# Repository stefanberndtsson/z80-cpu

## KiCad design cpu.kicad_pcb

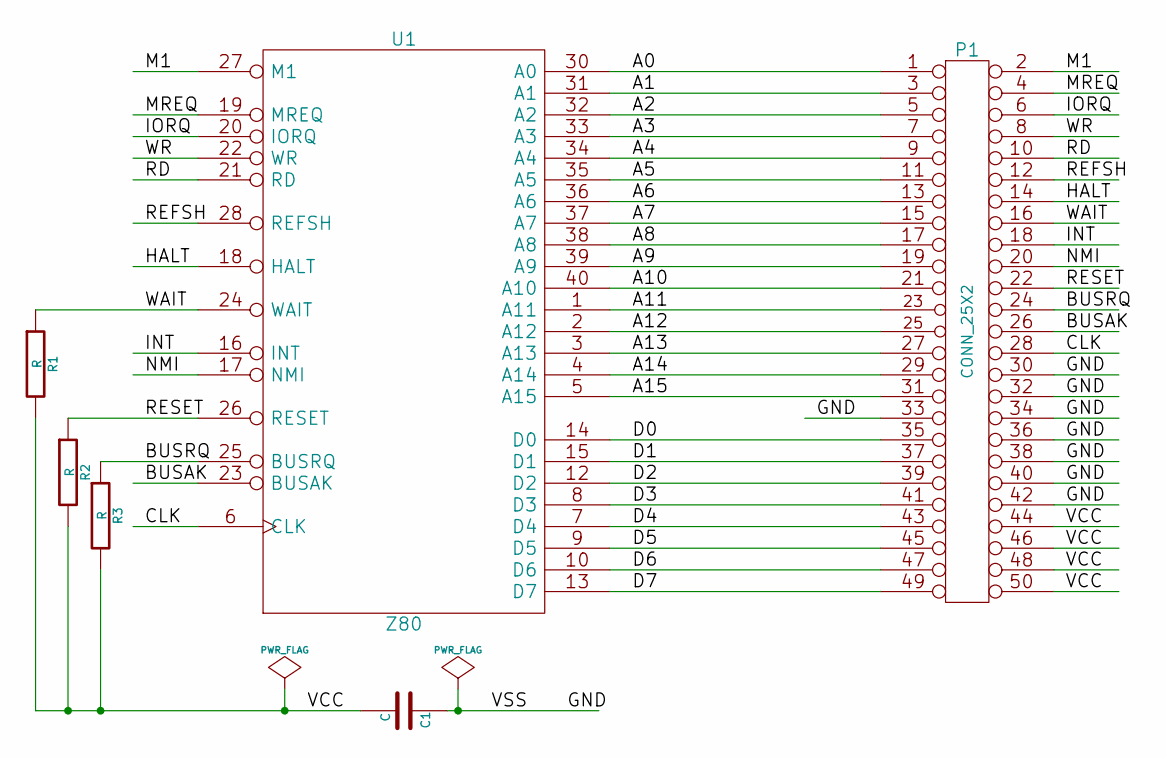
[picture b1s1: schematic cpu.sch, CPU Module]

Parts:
C1: C; Capacitor3MMDiscRM2.5
P1: CONN_25X2; Socket_Strip_Straight_2x25
R1, R2, R3: R; Resistor_Horizontal_RM10mm
U1: Z80; DIP-40__600_ELL

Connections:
/A0: P1.1, U1.30 (A0)
/A1: P1.3, U1.31 (A1)
/A2: P1.5, U1.32 (A2)
/A3: P1.7, U1.33 (A3)
/A4: P1.9, U1.34 (A4)
/A5: P1.11, U1.35 (A5)
/A6: P1.13, U1.36 (A6)
/A7: P1.15, U1.37 (A7)
/A8: P1.17, U1.38 (A8)
/A9: P1.19, U1.39 (A9)
/A10: P1.21, U1.40 (A10)
/A11: P1.23, U1.1 (A11)
/A12: P1.25, U1.2 (A12)
/A13: P1.27, U1.3 (A13)
/A14: P1.29, U1.4 (A14)
/A15: P1.31, U1.5 (A15)
/BUSAK: P1.26, U1.23 (BUSAK)
/BUSRQ: P1.24, R3.1, U1.25 (BUSRQ)
/CLK: P1.28, U1.6 (CLK)
/D0: P1.35, U1.14 (D0)
/D1: P1.37, U1.15 (D1)
/D2: P1.39, U1.12 (D2)
/D3: P1.41, U1.8 (D3)
/D4: P1.43, U1.7 (D4)
/D5: P1.45, U1.9 (D5)
/D6: P1.47, U1.10 (D6)
/D7: P1.49, U1.13 (D7)
/HALT: P1.14, U1.18 (HALT)
/INT: P1.18, U1.16 (INT)
/IORQ: P1.6, U1.20 (IORQ)
/M1: P1.2, U1.27 (M1)
/MREQ: P1.4, U1.19 (MREQ)
/NMI: P1.20, U1.17 (NMI)
/RD: P1.10, U1.21 (RD)
/REFSH: P1.12, U1.28 (REFSH)
/RESET: P1.22, R2.1, U1.26 (RESET)
/WAIT: P1.16, R1.1, U1.24 (WAIT)
/WR: P1.8, U1.22 (WR)
VCC: C1.2, P1.44, P1.46, P1.48, P1.50, R1.2, R2.2, R3.2, U1.11 (VCC)
VSS: C1.1, P1.30, P1.32, P1.33, P1.34, P1.36, P1.38, P1.40, P1.42, U1.29 (VSS)

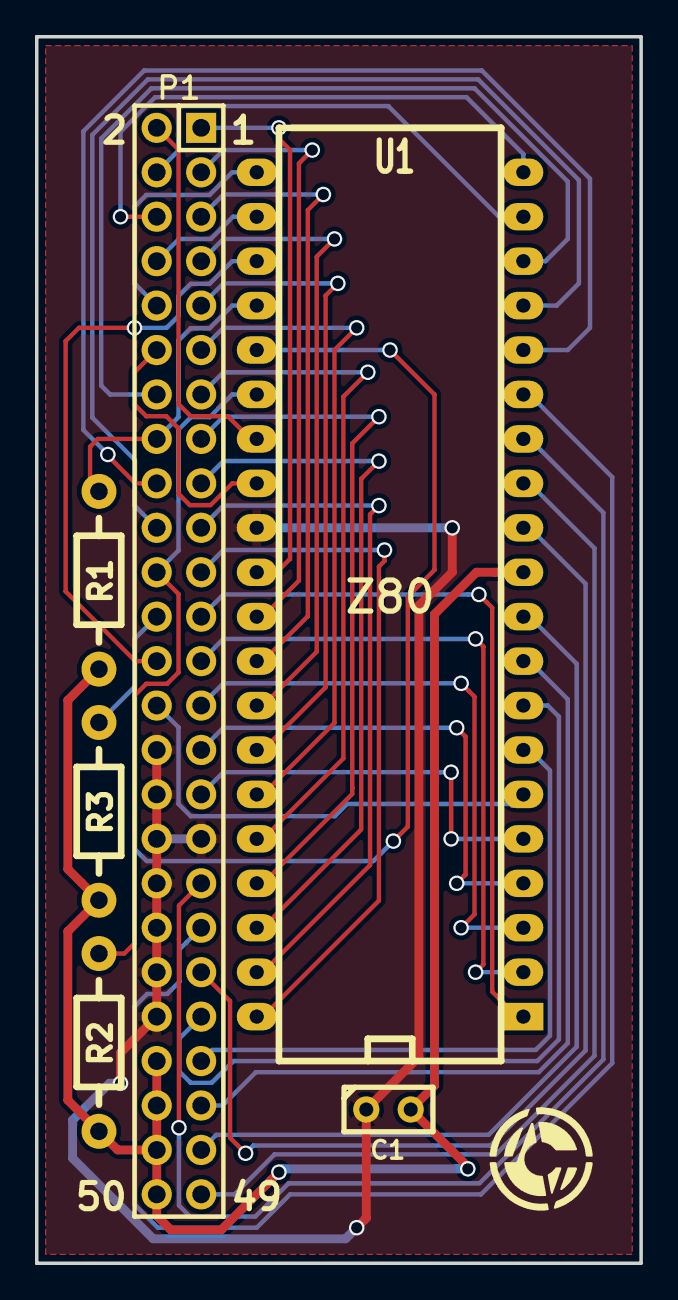
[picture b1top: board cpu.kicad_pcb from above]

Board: 2 copper layers, 34.5 x 70.1 mm, 6 parts (0 on the bottom side), 40 nets.

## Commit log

2014-08-15 Initial
